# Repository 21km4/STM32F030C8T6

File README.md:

# STM32F030C8T6

STM32F030C8T6の最小開発ボードです。KiCADのプロジェクトとなっています。
JLCPCBで発注すれば、全て基本パーツで作れるのでかなり割安で作成することができます。

各部品名、LCSCは打ち込み済みです。

無検証、無保証なので、使用する場合は必ず回路とボード図を確認すること。

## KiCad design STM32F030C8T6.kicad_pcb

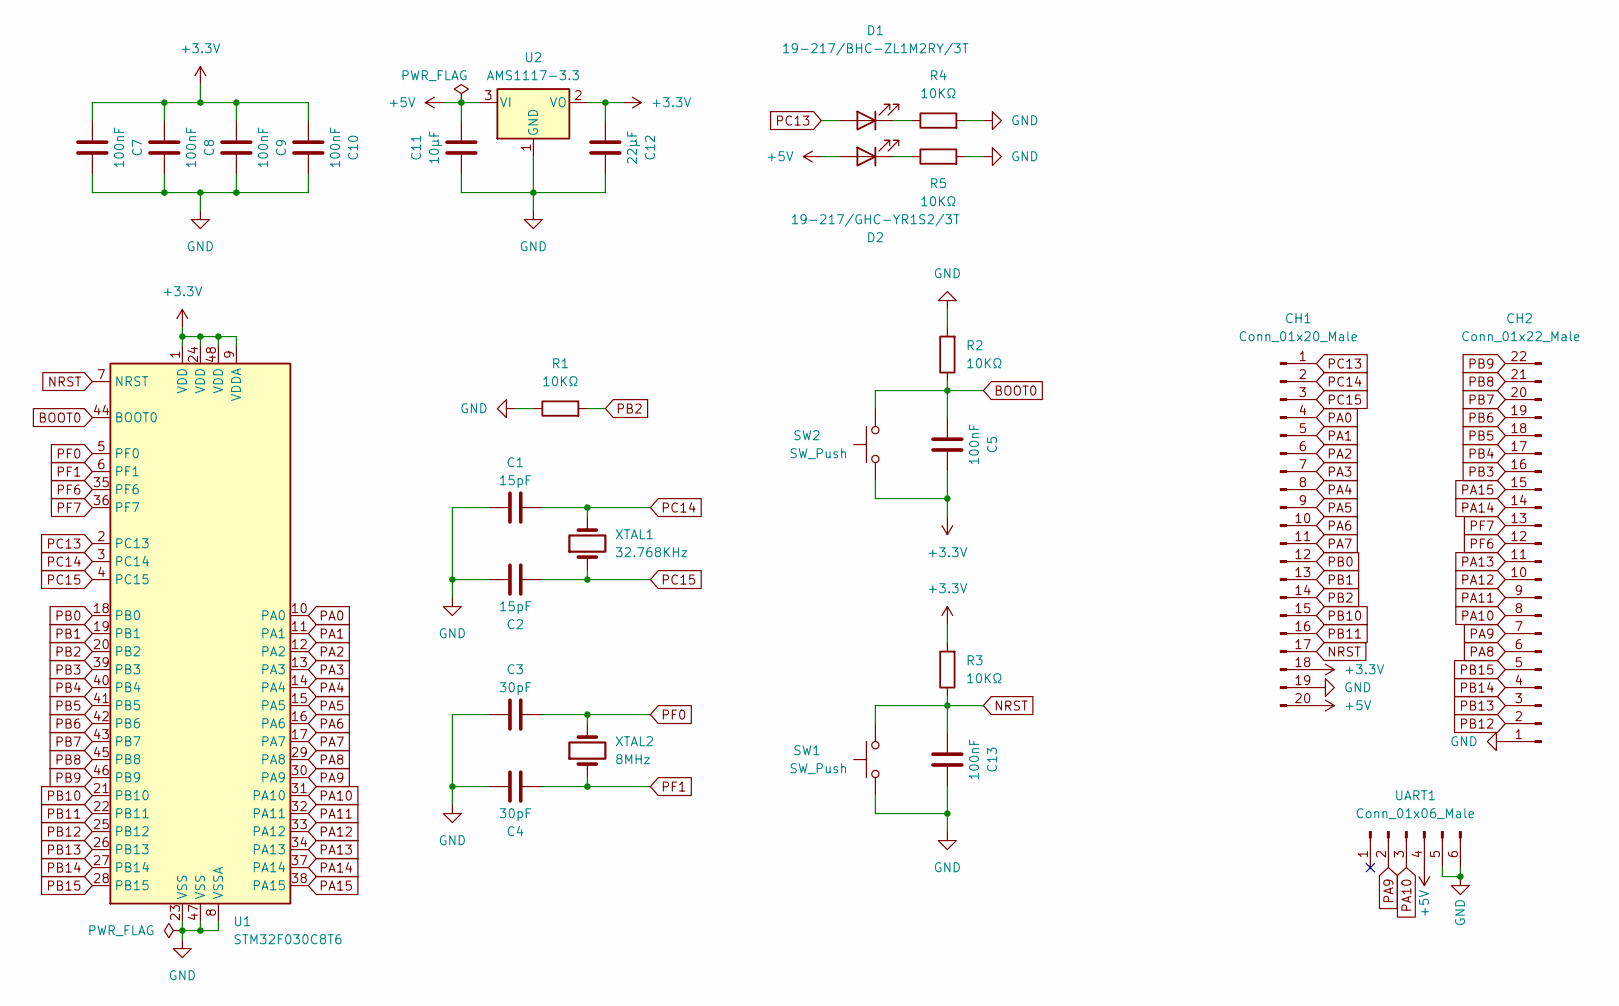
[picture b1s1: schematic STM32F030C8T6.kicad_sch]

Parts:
C1, C2: 15pF; C_0402_1005Metric; LCSC C1548
C3, C4: 30pF; C_0402_1005Metric; LCSC C1570
C5, C7, C8, C9, C10, C13: 100nF; C_0402_1005Metric; LCSC C1525
C11: 10μF; C_0603_1608Metric; LCSC C19702
C12: 22μF; C_0603_1608Metric; LCSC C59461
CH1: Conn_01x20_Male; PinHeader_1x20_P2.54mm_Vertical
CH2: Conn_01x22_Male; PinHeader_1x22_P2.54mm_Vertical
D1: 19-217/BHC-ZL1M2RY/3T; LED_0603_1608Metric; LCSC C72041
D2: 19-217/GHC-YR1S2/3T; LED_0603_1608Metric; LCSC C72043
R1, R2, R3, R4, R5: 10KΩ; R_0402_1005Metric; LCSC C25744
SW1, SW2: SW_Push; SW_SPST_TL3342; LCSC C318884
U1: STM32F030C8T6; LQFP-48_7x7mm_P0.5mm; LCSC C23922
U2: AMS1117-3.3; SOT-223-3_TabPin2; LCSC C6186
UART1: Conn_01x06_Male; PinHeader_1x06_P2.54mm_Vertical
XTAL1: 32.768KHz; Crystal_SMD_3215-2Pin_3.2x1.5mm; LCSC C32346
XTAL2: 8MHz; Crystal_SMD_HC49-SD; LCSC C12674

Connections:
+3.3V: C5.2, C7.1, C8.1, C9.1, C10.1, C12.1, CH1.18, R3.2, SW2.1, U1.1 (VDD), U1.9 (VDDA), U1.24 (VDD), U1.48 (VDD), U2.2 (VO)
+5V: C11.1, CH1.20, D2.2 (A), U2.3 (VI), UART1.4
BOOT0: C5.1, R2.1, SW2.2, U1.44 (BOOT0)
GND: C1.1, C2.1, C3.1, C4.1, C7.2, C8.2, C9.2, C10.2, C11.2, C12.2, C13.2, CH1.19, CH2.1, R1.1, R2.2, R4.2, R5.2, SW1.1, U1.8 (VSSA), U1.23 (VSS), U1.47 (VSS), U2.1 (GND), UART1.5, UART1.6
NRST: C13.1, CH1.17, R3.1, SW1.2, U1.7 (NRST)
unnamed: D1.1 (K), R4.1
unnamed: D2.1 (K), R5.1
PA0: CH1.4, U1.10 (PA0)
PA1: CH1.5, U1.11 (PA1)
PA2: CH1.6, U1.12 (PA2)
PA3: CH1.7, U1.13 (PA3)
PA4: CH1.8, U1.14 (PA4)
PA5: CH1.9, U1.15 (PA5)
PA6: CH1.10, U1.16 (PA6)
PA7: CH1.11, U1.17 (PA7)
PA8: CH2.6, U1.29 (PA8)
PA9: CH2.7, U1.30 (PA9), UART1.2
PA10: CH2.8, U1.31 (PA10), UART1.3
PA11: CH2.9, U1.32 (PA11)
PA12: CH2.10, U1.33 (PA12)
PA13: CH2.11, U1.34 (PA13)
PA14: CH2.14, U1.37 (PA14)
PA15: CH2.15, U1.38 (PA15)
PB0: CH1.12, U1.18 (PB0)
PB1: CH1.13, U1.19 (PB1)
PB2: CH1.14, R1.2, U1.20 (PB2)
PB3: CH2.16, U1.39 (PB3)
PB4: CH2.17, U1.40 (PB4)
PB5: CH2.18, U1.41 (PB5)
PB6: CH2.19, U1.42 (PB6)
PB7: CH2.20, U1.43 (PB7)
PB8: CH2.21, U1.45 (PB8)
PB9: CH2.22, U1.46 (PB9)
PB10: CH1.15, U1.21 (PB10)
PB11: CH1.16, U1.22 (PB11)
PB12: CH2.2, U1.25 (PB12)
PB13: CH2.3, U1.26 (PB13)
PB14: CH2.4, U1.27 (PB14)
PB15: CH2.5, U1.28 (PB15)
PC13: CH1.1, D1.2 (A), U1.2 (PC13)
PC14: C1.2, CH1.2, U1.3 (PC14), XTAL1.2
PC15: C2.2, CH1.3, U1.4 (PC15), XTAL1.1
PF0: C3.2, U1.5 (PF0), XTAL2.2
PF1: C4.2, U1.6 (PF1), XTAL2.1
PF6: CH2.12, U1.35 (PF6)
PF7: CH2.13, U1.36 (PF7)

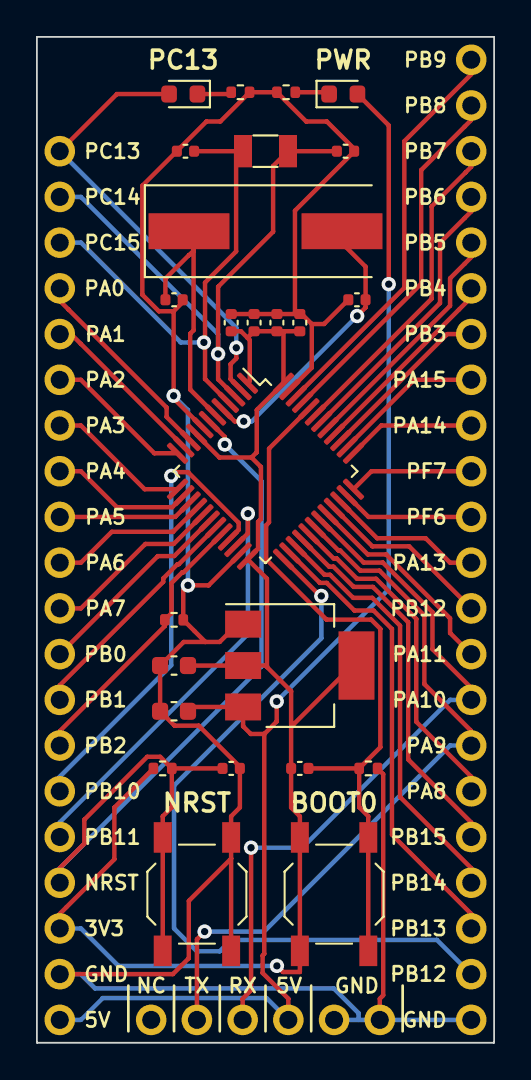
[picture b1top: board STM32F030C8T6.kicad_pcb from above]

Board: 2 copper layers, 25.4 x 55.9 mm, 28 parts (0 on the bottom side), 46 nets.

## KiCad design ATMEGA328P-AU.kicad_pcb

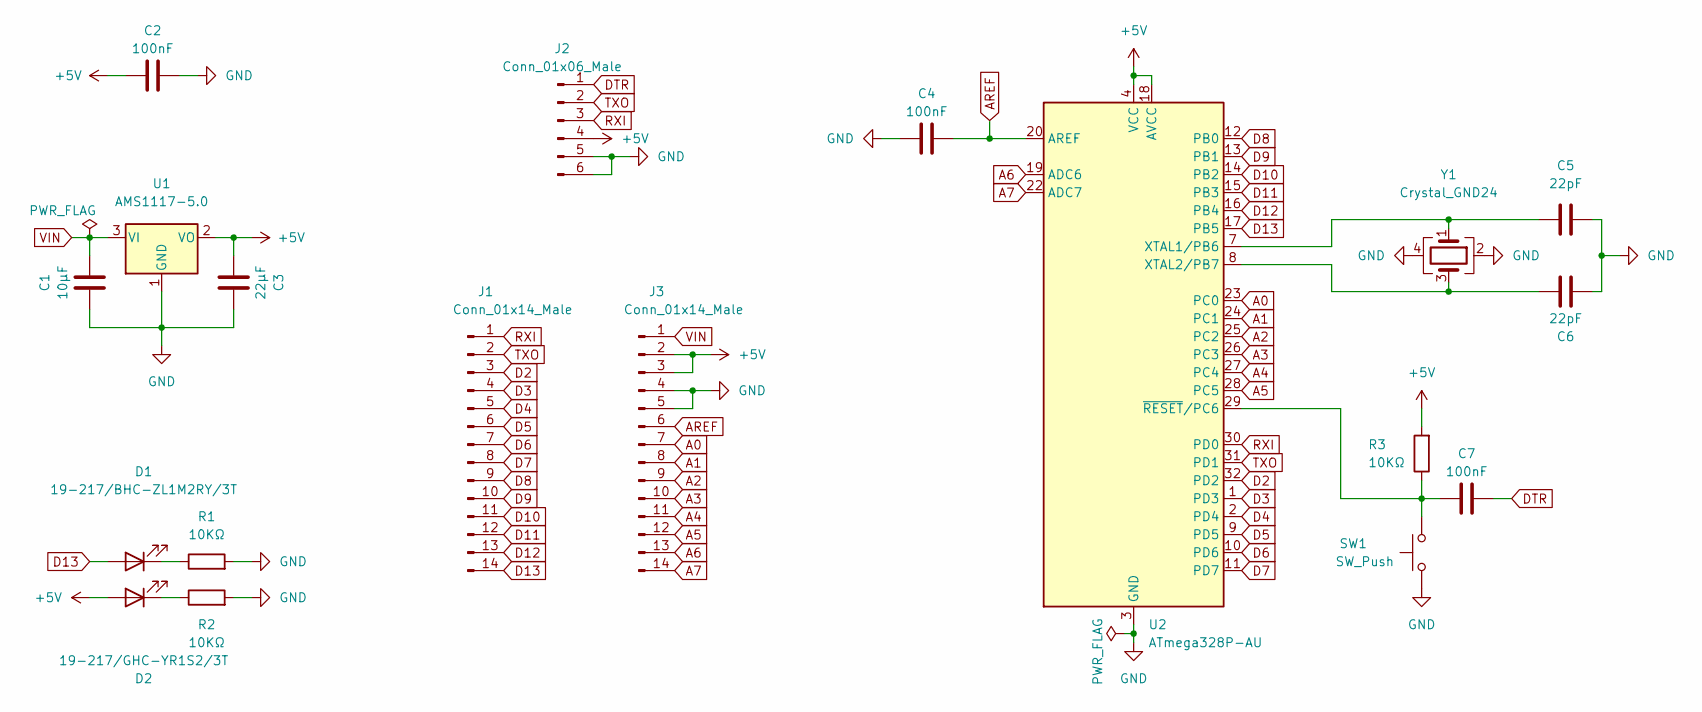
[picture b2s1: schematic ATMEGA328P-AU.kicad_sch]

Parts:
C1: 10μF; C_0603_1608Metric; LCSC C19702
C2, C4, C7: 100nF; C_0402_1005Metric; LCSC C1525
C3: 22μF; C_0603_1608Metric; LCSC C59461
C5, C6: 22pF; C_0402_1005Metric; LCSC C1555
D1: 19-217/BHC-ZL1M2RY/3T; LED_0603_1608Metric; LCSC C72041
D2: 19-217/GHC-YR1S2/3T; LED_0603_1608Metric; LCSC C72043
J1, J3: Conn_01x14_Male; PinHeader_1x14_P2.54mm_Vertical
J2: Conn_01x06_Male; PinHeader_1x06_P2.54mm_Vertical
R1, R2, R3: 10KΩ; R_0402_1005Metric; LCSC C25744
SW1: SW_Push; SW_SPST_TL3342; LCSC C318884
U1: AMS1117-5.0; SOT-223-3_TabPin2
U2: ATmega328P-AU; TQFP-32_7x7mm_P0.8mm; LCSC C14877
Y1: Crystal_GND24; Crystal_SMD_3225-4Pin_3.2x2.5mm; LCSC C13738

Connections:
+5V: C2.1, C3.1, D2.2 (A), J2.4, J3.2, J3.3, R3.2, U1.2 (VO), U2.4 (VCC), U2.6 (VCC), U2.18 (AVCC)
A0: J3.7, U2.23 (PC0)
A1: J3.8, U2.24 (PC1)
A2: J3.9, U2.25 (PC2)
A3: J3.10, U2.26 (PC3)
A4: J3.11, U2.27 (PC4)
A5: J3.12, U2.28 (PC5)
A6: J3.13, U2.19 (ADC6)
A7: J3.14, U2.22 (ADC7)
AREF: C4.2, J3.6, U2.20 (AREF)
D2: J1.3, U2.32 (PD2)
D3: J1.4, U2.1 (PD3)
D4: J1.5, U2.2 (PD4)
D5: J1.6, U2.9 (PD5)
D6: J1.7, U2.10 (PD6)
D7: J1.8, U2.11 (PD7)
D8: J1.9, U2.12 (PB0)
D9: J1.10, U2.13 (PB1)
D10: J1.11, U2.14 (PB2)
D11: J1.12, U2.15 (PB3)
D12: J1.13, U2.16 (PB4)
D13: D1.2 (A), J1.14, U2.17 (PB5)
DTR: C7.2, J2.1
GND: C1.2, C2.2, C3.2, C4.1, C5.2, C6.2, J2.5, J2.6, J3.4, J3.5, R1.2, R2.2, SW1.1, U1.1 (GND), U2.3 (GND), U2.5 (GND), U2.21 (GND), Y1.2, Y1.4
unnamed: C5.1, U2.7 (XTAL1/PB6), Y1.1
unnamed: C6.1, U2.8 (XTAL2/PB7), Y1.3
unnamed: C7.1, R3.1, SW1.2, U2.29 (~RESET/PC6)
unnamed: D1.1 (K), R1.1
unnamed: D2.1 (K), R2.1
RXI: J1.1, J2.3, U2.30 (PD0)
TXO: J1.2, J2.2, U2.31 (PD1)
VIN: C1.1, J3.1, U1.3 (VI)

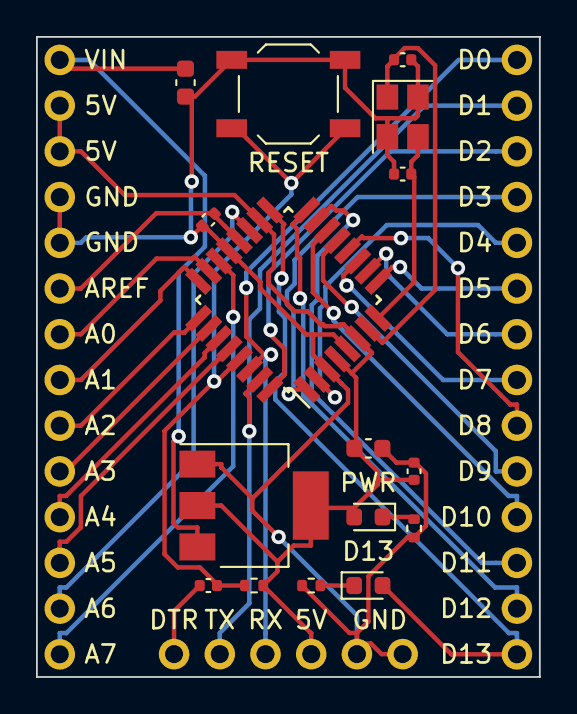
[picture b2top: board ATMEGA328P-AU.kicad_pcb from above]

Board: 2 copper layers, 27.9 x 35.6 mm, 19 parts (0 on the bottom side), 32 nets.

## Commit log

2022-09-29 Create LICENSE
